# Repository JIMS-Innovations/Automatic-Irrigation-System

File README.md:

# Automatic-Irrigation-System
Firmware for an automatic irrigation device.

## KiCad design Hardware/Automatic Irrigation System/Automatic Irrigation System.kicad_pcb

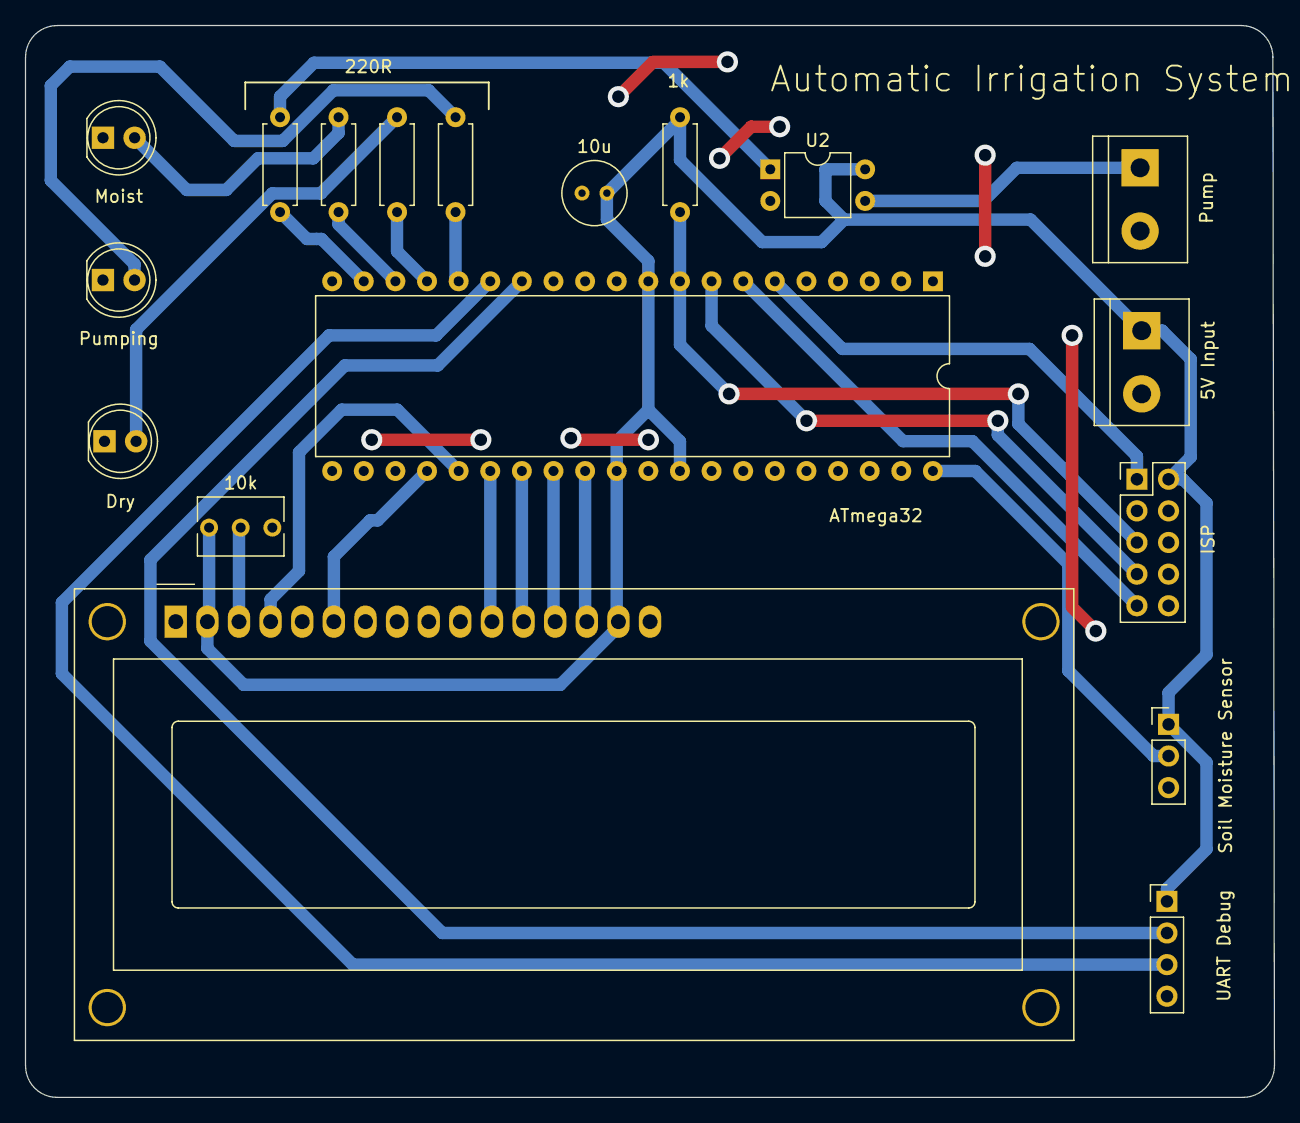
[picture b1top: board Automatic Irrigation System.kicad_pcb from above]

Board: 2 copper layers, 100.3 x 86.1 mm, 18 parts (0 on the bottom side), 25 nets.

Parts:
C1: 10u; C_Radial_D5.0mm_H5.0mm_P2.00mm
D1: Pumping; LED_D5.0mm
D2: Dry; LED_D5.0mm
D3: Moist; LED_D5.0mm
DS1: WC1602A
J1: Pump; TerminalBlock_bornier-2_P5.08mm
J2: Soil Moisture Sensor; PinHeader_1x03_P2.54mm_Vertical
J3: 5V Input; TerminalBlock_bornier-2_P5.08mm
J4: UART Debug; PinHeader_1x04_P2.54mm_Vertical
J5: ISP; PinHeader_2x05_P2.54mm_Vertical
R1: 1k; R_Axial_DIN0207_L6.3mm_D2.5mm_P7.62mm_Horizontal
R2, R3, R4, R5: 220R; R_Axial_DIN0207_L6.3mm_D2.5mm_P7.62mm_Horizontal
RV1: 10k; Potentiometer_Bourns_3266Y_Vertical
U1: ATmega32; DIP-40_W15.24mm
U2: PC817; DIP-4_W7.62mm

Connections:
+5V: C1.1, DS1.2 (VDD), DS1.15 (LED(+)), J2.1, J3.1, J4.1, J5.2, R1.1, RV1.1, U1.10 (VCC), U1.30 (AVCC), U1.32 (AREF), U2.4
/LED_1: R3.1, U1.16 (PD2)
/LED_2: R4.1, U1.17 (PD3)
/LED_3: R5.1, U1.18 (PD4)
/MISO: J5.9, U1.7 (PB6)
/MOSI: J5.1, U1.6 (PB5)
/PUMP_SIG: R2.1, U1.19 (PD5)
/RESET: J5.5, R1.2, U1.9 (~RESET)
/RXD: J4.2, U1.14 (PD0)
/SCK: J5.7, U1.8 (PB7)
/TXD: J4.3, U1.15 (PD1)
GND: C1.2, D1.1 (K), D2.1 (K), D3.1 (K), DS1.1 (VSS), DS1.5 (R/W), DS1.16 (LED(-)), J1.2, J2.3, J3.2, J4.4, J5.4, J5.6, J5.8, J5.10, RV1.3, U1.11 (GND), U1.31 (GND), U2.2
unnamed: D1.2 (A), R3.2
unnamed: D2.2 (A), R4.2
unnamed: D3.2 (A), R5.2
unnamed: DS1.11 (D4), U1.26 (PC4)
unnamed: DS1.12 (D5), U1.27 (PC5)
unnamed: DS1.13 (D6), U1.28 (PC6)
unnamed: DS1.14 (D7), U1.29 (PC7)
unnamed: DS1.6 (E), U1.24 (PC2)
unnamed: DS1.4 (RS), U1.25 (PC3)
unnamed: DS1.3 (VO), RV1.2
unnamed: J1.1, U2.3
unnamed: J2.2, U1.40 (PA0)
unnamed: R2.2, U2.1

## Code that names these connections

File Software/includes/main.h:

/**
 * @file main.h
 * @author Jesutofunmi Kupoluyi (jimsufficency@gmail.com)
 * @brief This is the header file for the main.c/.cpp source file.
 * @version 0.1
 * @date 2023-09-06
 * 
 * @copyright Copyright (c) 2023
 * 
 */

#ifndef __MAIN_H__
#define __MAIN_H__

/* Defines */
#define F_CPU 8000000UL

/* Including required libraries */
#include <avr/io.h>
/* #include <avr/iom328p.h> */ /* For atmega328p */
#include <util/delay.h>
#include <avr/interrupt.h>
#include <stdio.h>


/** List of components
 * LEDs [3] -> Moist, Pumping and Dry
 * LCD  [1] -> 1602A (4-bit mode)
 * Pump [1] (via Optocoupler)
 * Soil Moisture sensor [1] (via ADC)
 * UART debug output [1]
*/

/* LCD pin definitions */
#define LCD_D4      PC4
#define LCD_D5      PC5
#define LCD_D6      PC6
#define LCD_D7      PC7
#define LCD_RS      PC3
#define LCD_E       PC2
#define LCD_PORT    PORTC
#define LCD_DDR     DDRC

/* LED pin definitions */
#define PUMPING_LED     PD2
#define DRY_LED         PD3
#define MOIST_LED       PD4
#define LED_PORT        PORTD
#define LED_DDR         DDRD

/* Pump pin definitions */
#define PUMP_PIN        PD5
#define PUMP_PORT       PORTD
#define PUMP_DDR        DDRD

/* Soil moisture sensor pin definitions */
#define MOIST_SENSE_PIN     PA0
#define MOIST_SENSE_PORT    PORTA
#define MOIST_SENSE_DDR     DDRA

/* Soil moisture sensor calibration values */
#define SOIL_WET 450
#define SOIL_DRY 750


#endif/*__MAIN_H__*/

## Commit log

2023-10-14 Initialization
